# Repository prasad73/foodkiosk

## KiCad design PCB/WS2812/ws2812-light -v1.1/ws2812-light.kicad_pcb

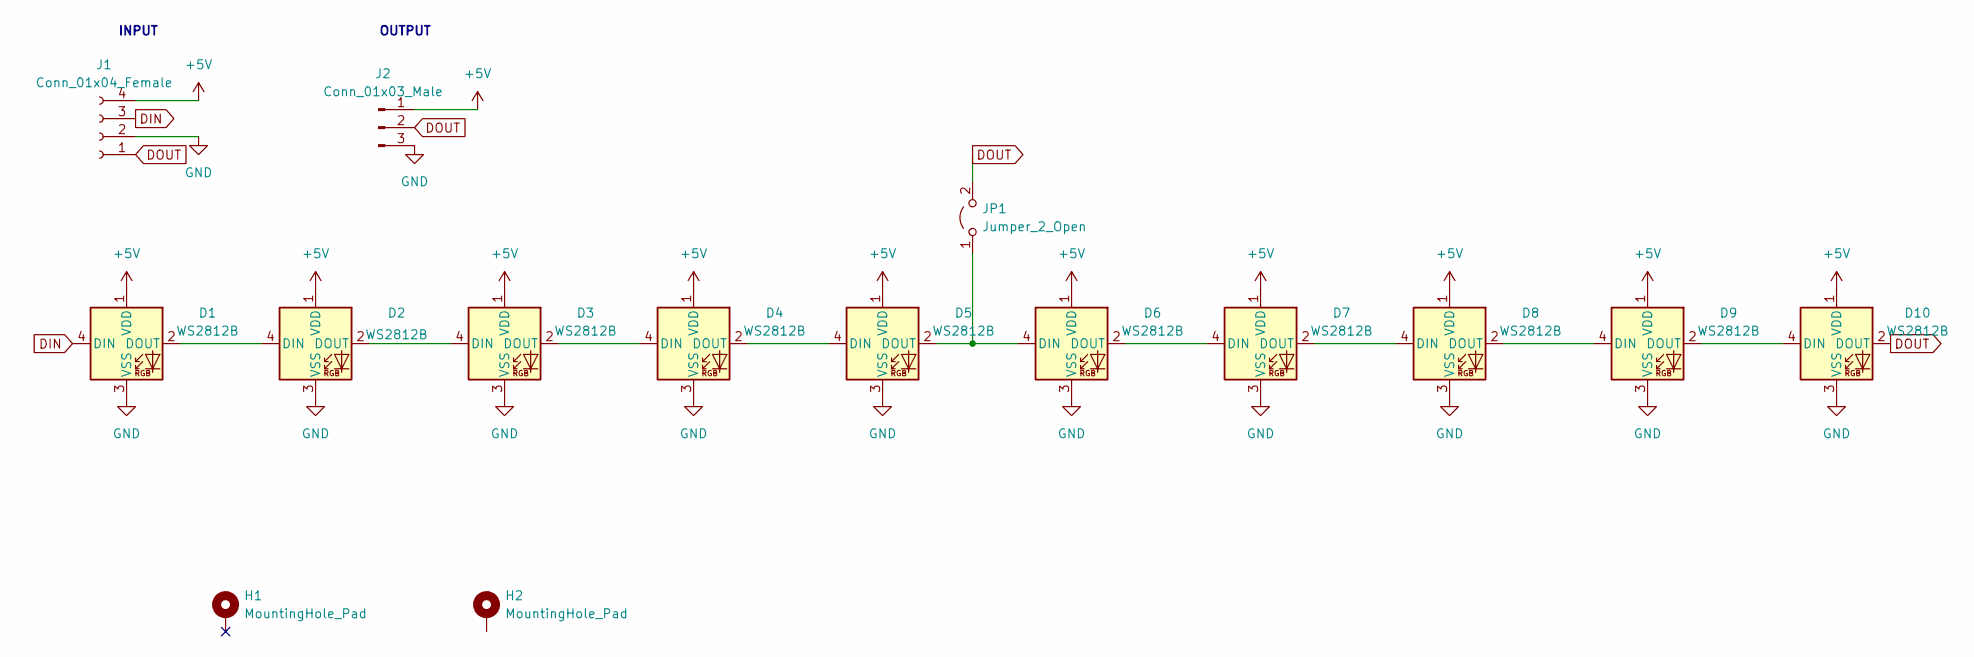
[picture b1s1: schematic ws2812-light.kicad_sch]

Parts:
D1, D2, D3, D4, D5, D6, D7, D8, D9, D10: WS2812B; LED_WS2812B_PLCC4_5.0x5.0mm_P3.2mm
H1, H2: MountingHole_Pad; MountingHole_3.2mm_M3_ISO7380_Pad
J1: Conn_01x04_Female; JST_XH_B4B-XH-A_1x04_P2.50mm_Vertical
J2: Conn_01x03_Male; PinHeader_1x03_P2.54mm_Vertical
JP1: Jumper_2_Open; SolderJumper-2_P1.3mm_Open_RoundedPad1.0x1.5mm

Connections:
+5V: D1.1 (VDD), D2.1 (VDD), D3.1 (VDD), D4.1 (VDD), D5.1 (VDD), D6.1 (VDD), D7.1 (VDD), D8.1 (VDD), D9.1 (VDD), D10.1 (VDD), J1.4, J2.1
DIN: D1.4 (DIN), J1.3
DOUT: D10.2 (DOUT), J1.1, J2.2, JP1.2 (B)
GND: D1.3 (VSS), D2.3 (VSS), D3.3 (VSS), D4.3 (VSS), D5.3 (VSS), D6.3 (VSS), D7.3 (VSS), D8.3 (VSS), D9.3 (VSS), D10.3 (VSS), J1.2, J2.3
unnamed: D1.2 (DOUT), D2.4 (DIN)
unnamed: D2.2 (DOUT), D3.4 (DIN)
unnamed: D3.2 (DOUT), D4.4 (DIN)
unnamed: D4.2 (DOUT), D5.4 (DIN)
unnamed: D5.2 (DOUT), D6.4 (DIN), JP1.1 (A)
unnamed: D6.2 (DOUT), D7.4 (DIN)
unnamed: D7.2 (DOUT), D8.4 (DIN)
unnamed: D8.2 (DOUT), D9.4 (DIN)
unnamed: D9.2 (DOUT), D10.4 (DIN)

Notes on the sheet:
INPUT
OUTPUT

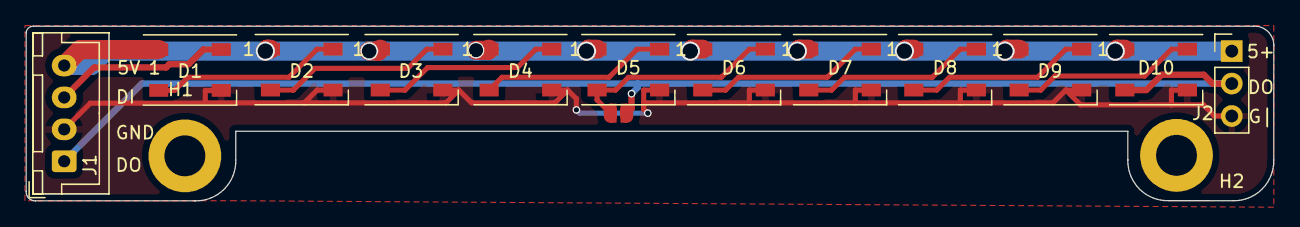
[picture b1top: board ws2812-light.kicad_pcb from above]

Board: 2 copper layers, 97.7 x 13.7 mm, 16 parts (1 on the bottom side), 13 nets.

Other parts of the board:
G2: LOGO; Verifygn-Logo-Tiny

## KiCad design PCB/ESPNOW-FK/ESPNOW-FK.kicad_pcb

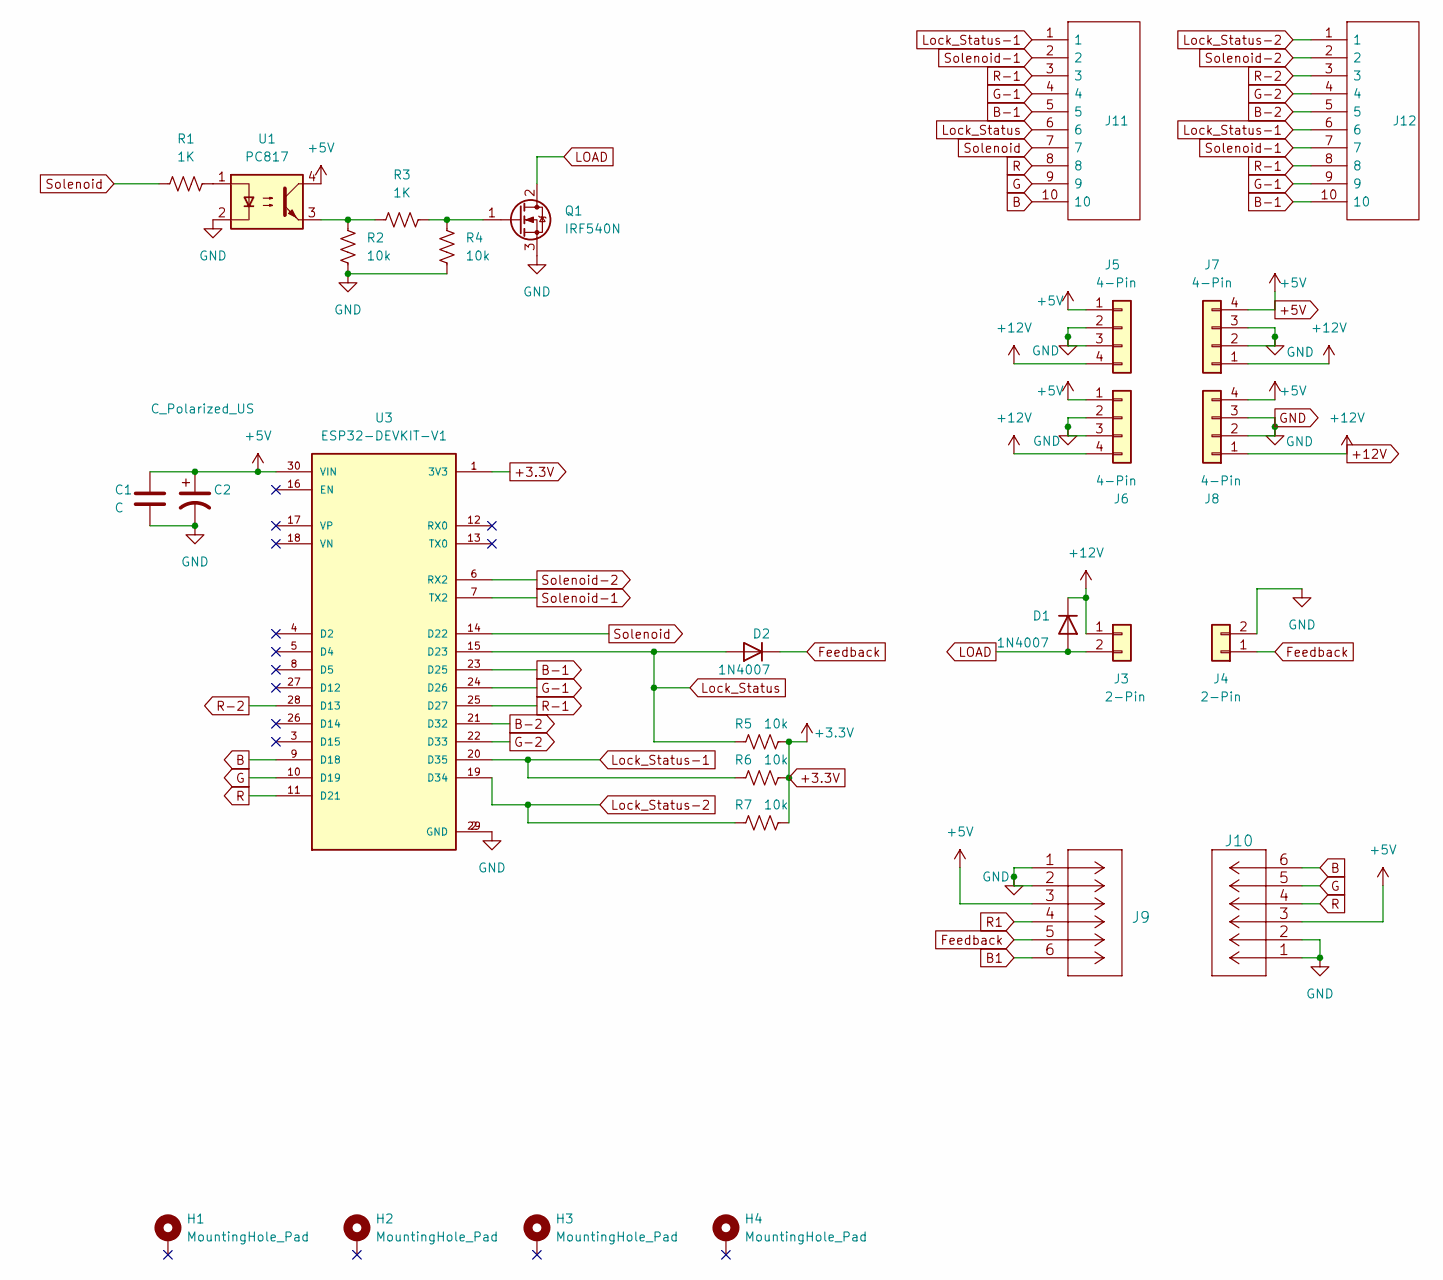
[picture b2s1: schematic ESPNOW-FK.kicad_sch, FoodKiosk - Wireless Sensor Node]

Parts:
C1: C; C_Disc_D5.0mm_W2.5mm_P5.00mm
C2: C_Polarized_US; CP_Radial_D8.0mm_P5.00mm
D1, D2: 1N4007; D_DO-41_SOD81_P10.16mm_Horizontal
H1, H2, H3, H4: MountingHole_Pad; MountingHole_3.7mm_Pad
J3, J4: 2-Pin; JST_XH_1x02_P2.50mm_Vertical
J5, J7: 4-Pin; TerminalBlock_Phoenix_1x04_P5.08mm_Horizontal
J6, J8: 4-Pin; JST_XH_1x04_P2.50mm_Vertical
J9, J10: 6-Pin; JST_XH_1x06_P2.50mm_Vertical
J11, J12: 10-Pin; JST_XH_1x10_P2.50mm_Vertical; Manufacturer_Part_Number 1792944; Mouser Part Number 651-1792944
Q1: IRF540N; TO-220-3_Vertical
R1, R3: 1K; R_Axial_DIN0207_L6.3mm_D2.5mm_P10.16mm_Horizontal
R2, R4, R5, R6, R7: 10k; R_Axial_DIN0207_L6.3mm_D2.5mm_P10.16mm_Horizontal
U1: PC817; DIP-4_W7.62mm
U3: ESP32-DEVKIT-V1; MODULE_ESP32_DEVKIT_V1; PARTREV N/A

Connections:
+3.3V: R5.2, R6.2, R7.2, U3.1 (3V3)
+5V: C1.1, C2.1, J5.1, J6.1, J7.4, J8.4, J9.3, J10.3, U1.4, U3.30 (VIN)
+12V: D1.1 (K), J3.1, J5.4, J6.4, J7.1, J8.1
B: J10.6, J11.10, U3.9 (D18)
B1: J9.6
B-1: J11.5, J12.10, U3.23 (D25)
B-2: J12.5, U3.21 (D32)
Feedback: D2.1 (K), J4.1, J9.5
G: J10.5, J11.9, U3.10 (D19)
G-1: J11.4, J12.9, U3.24 (D26)
G-2: J12.4, U3.22 (D33)
GND: C1.2, C2.2, J4.2, J5.2, J5.3, J6.2, J6.3, J7.2, J7.3, J8.2, J8.3, J9.1, J9.2, J10.1, J10.2, Q1.3 (S), R2.2, R4.2, U1.2, U3.2 (GND), U3.29 (GND)
LOAD: D1.2 (A), J3.2, Q1.2 (D)
Lock_Status: D2.2 (A), J11.6, R5.1, U3.15 (D23)
Lock_Status-1: J11.1, J12.6, R6.1, U3.20 (D35)
Lock_Status-2: J12.1, R7.1, U3.19 (D34)
unnamed: Q1.1 (G), R3.2, R4.1
unnamed: R1.2, U1.1
unnamed: R2.1, R3.1, U1.3
R: J10.4, J11.8, U3.11 (D21)
R1: J9.4
R-1: J11.3, J12.8, U3.25 (D27)
R-2: J12.3, U3.28 (D13)
Solenoid: J11.7, R1.1, U3.14 (D22)
Solenoid-1: J11.2, J12.7, U3.7 (TX2)
Solenoid-2: J12.2, U3.6 (RX2)

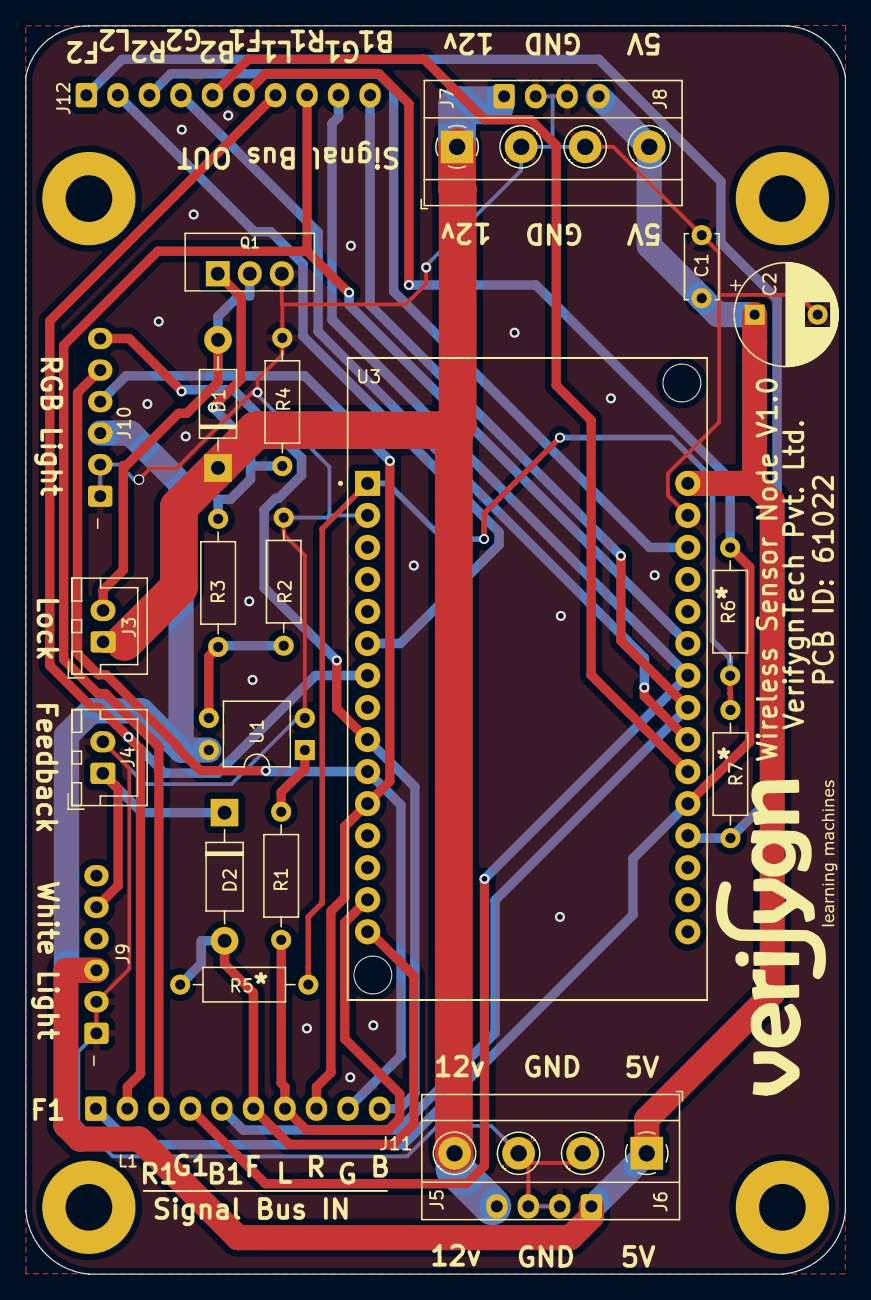
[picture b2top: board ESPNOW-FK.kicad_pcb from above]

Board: 2 copper layers, 65.0 x 99.0 mm, 30 parts (1 on the bottom side), 24 nets.

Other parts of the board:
G12132: LOGO; Verifygn-Logo-Small
G*3e2: LOGO; Verifygn-Logo-Small

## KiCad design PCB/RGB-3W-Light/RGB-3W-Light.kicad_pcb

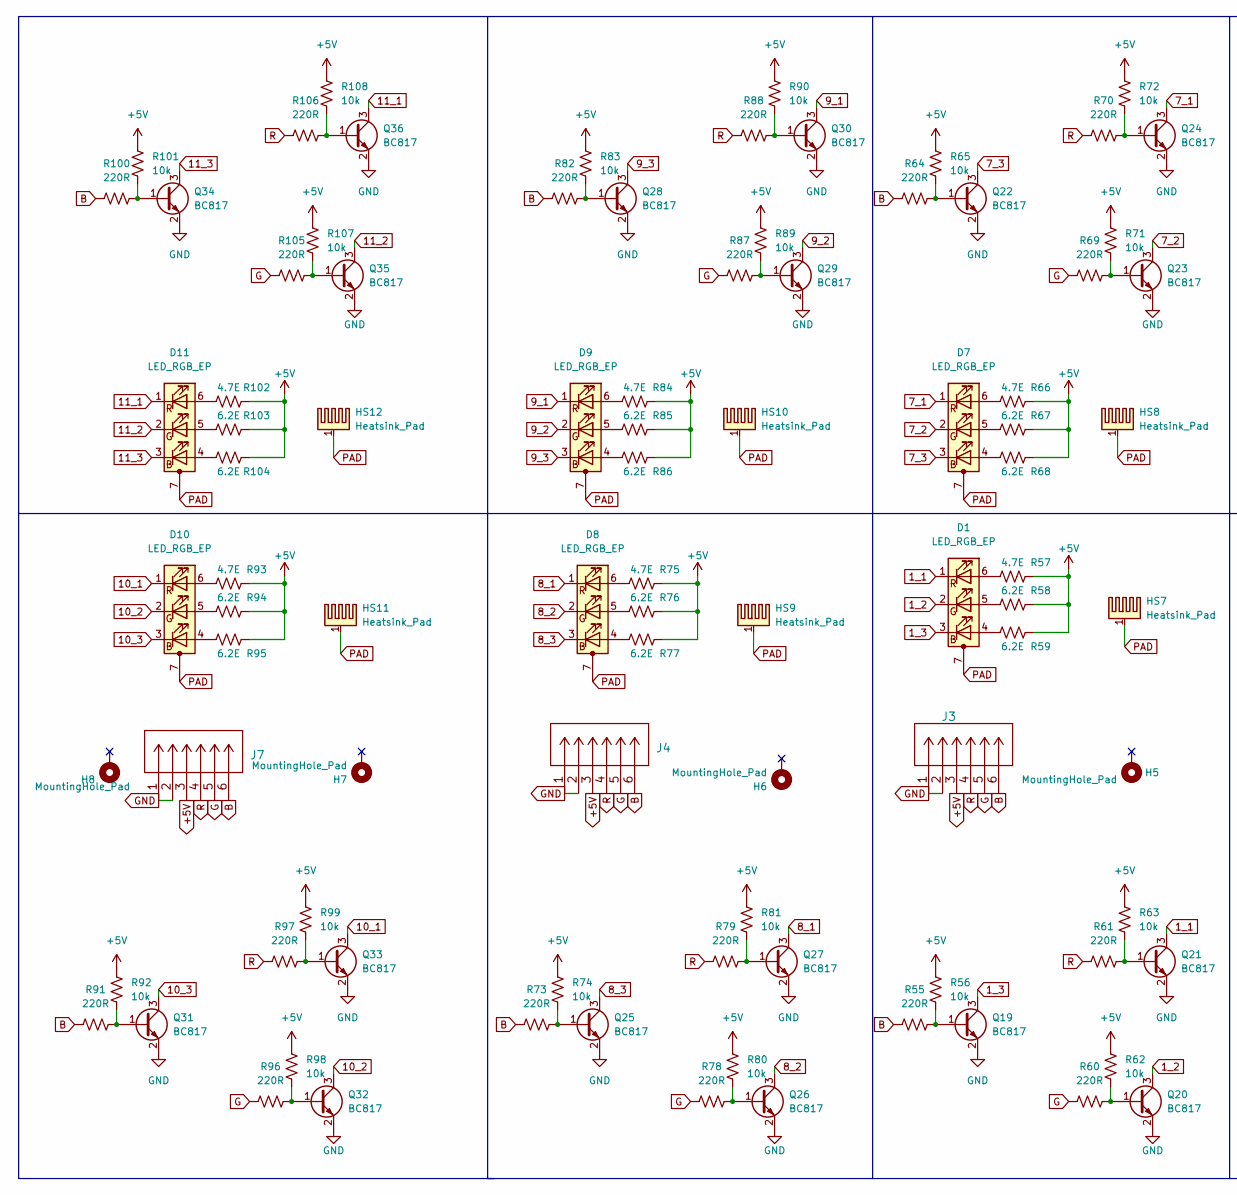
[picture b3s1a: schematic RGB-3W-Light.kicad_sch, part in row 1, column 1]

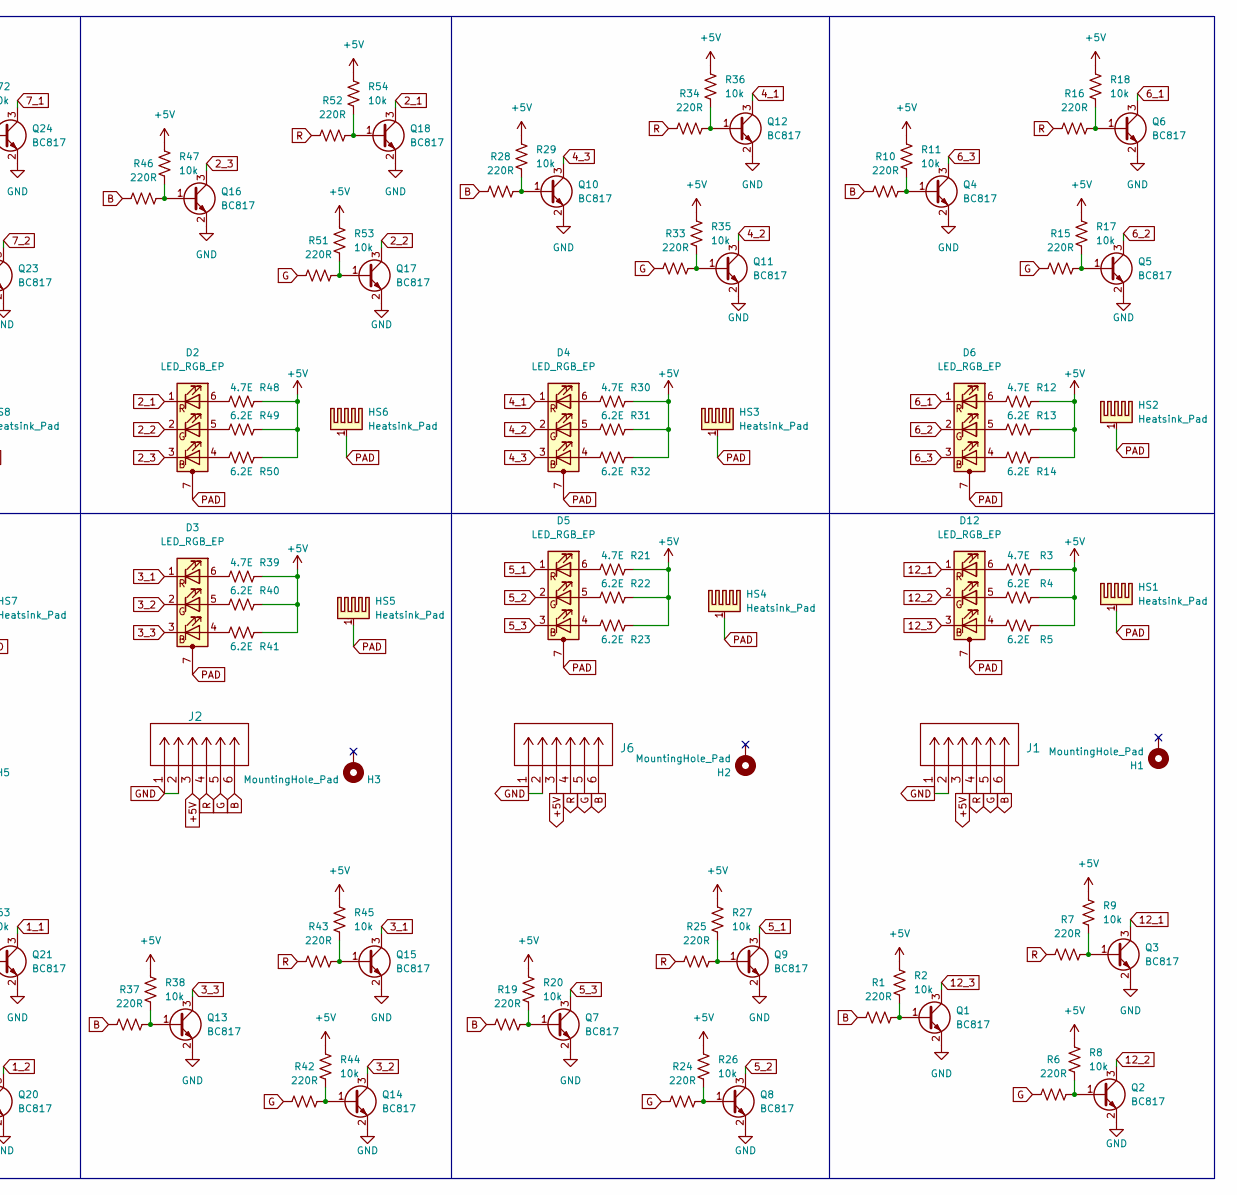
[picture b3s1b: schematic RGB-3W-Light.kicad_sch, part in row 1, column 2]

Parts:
D1, D2, D3, D4, D5, D6, D7, D8, D9, D10, D11, D12: LED_RGB_EP; LED_RGB_GT-P6PRGB4303
H1, H2, H3, H5, H6, H7, H8: MountingHole_Pad; MountingHole_3.5mm_Pad_Via
HS1, HS4, HS5, HS7, HS9, HS11: Heatsink_Pad; LED_COOLING_PAD
HS2, HS3, HS6, HS8, HS10: Heatsink_Pad; LED_COOLING_PAD-2
HS12: Heatsink_Pad; LED_COOLING_PAD-3
J1, J2, J3, J4, J6, J7: 6-Pin; JST_XH_1x06_P2.50mm_Vertical
Q1, Q2, Q3, Q4, Q5, Q6, Q7, Q8, Q9, Q10, Q11, Q12, Q13, Q14, Q15, Q16, Q17, Q18, Q19, Q20, Q21, Q22, Q23, Q24, Q25, Q26, Q27, Q28, Q29, Q30, Q31, Q32, Q33, Q34, Q35, Q36: BC817; SOT-23
R1, R6, R7, R10, R15, R16, R19, R24, R25, R28, R33, R34, R37, R42, R43, R46, R51, R52, R55, R60, R61, R64, R69, R70, R73, R78, R79, R82, R87, R88, R91, R96, R97, R100, R105, R106: 220R; R_0805_2012Metric_Pad1.20x1.40mm_HandSolder
R2, R8, R9, R11, R17, R18, R20, R26, R27, R29, R35, R36, R38, R44, R45, R47, R53, R54, R56, R62, R63, R65, R71, R72, R74, R80, R81, R83, R89, R90, R92, R98, R99, R101, R107, R108: 10k; R_0805_2012Metric_Pad1.20x1.40mm_HandSolder
R3, R12, R21, R30, R39, R48, R57, R66, R75, R84, R93, R102: 4.7E; R_2512_6332Metric_Pad1.40x3.35mm_HandSolder
R4, R5, R13, R14, R22, R23, R31, R32, R40, R41, R49, R50, R58, R59, R67, R68, R76, R77, R85, R86, R94, R95, R103, R104: 6.2E; R_2512_6332Metric_Pad1.40x3.35mm_HandSolder

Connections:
1_1: D1.1 (RK), Q21.3 (C)
1_2: D1.2 (GK), Q20.3 (C)
1_3: D1.3 (BK), Q19.3 (C)
2_1: D2.1 (RK), Q18.3 (C)
2_2: D2.2 (GK), Q17.3 (C)
2_3: D2.3 (BK), Q16.3 (C)
3_1: D3.1 (RK), Q15.3 (C)
3_2: D3.2 (GK), Q14.3 (C)
3_3: D3.3 (BK), Q13.3 (C)
4_1: D4.1 (RK), Q12.3 (C)
4_2: D4.2 (GK), Q11.3 (C)
4_3: D4.3 (BK), Q10.3 (C)
5_1: D5.1 (RK), Q9.3 (C)
5_2: D5.2 (GK), Q8.3 (C)
5_3: D5.3 (BK), Q7.3 (C)
6_1: D6.1 (RK), Q6.3 (C)
6_2: D6.2 (GK), Q5.3 (C)
6_3: D6.3 (BK), Q4.3 (C)
7_1: D7.1 (RK), Q24.3 (C)
7_2: D7.2 (GK), Q23.3 (C)
7_3: D7.3 (BK), Q22.3 (C)
8_1: D8.1 (RK), Q27.3 (C)
8_2: D8.2 (GK), Q26.3 (C)
8_3: D8.3 (BK), Q25.3 (C)
9_1: D9.1 (RK), Q30.3 (C)
9_2: D9.2 (GK), Q29.3 (C)
9_3: D9.3 (BK), Q28.3 (C)
10_1: D10.1 (RK), Q33.3 (C)
10_2: D10.2 (GK), Q32.3 (C)
10_3: D10.3 (BK), Q31.3 (C)
11_1: D11.1 (RK), Q36.3 (C)
11_2: D11.2 (GK), Q35.3 (C)
11_3: D11.3 (BK), Q34.3 (C)
12_1: D12.1 (RK), Q3.3 (C)
12_2: D12.2 (GK), Q2.3 (C)
12_3: D12.3 (BK), Q1.3 (C)
+5V: J1.3, J2.3, J3.3, J4.3, J6.3, J7.3, R2.1, R3.1, R4.1, R5.1, R8.1, R9.1, R11.1, R12.1, R13.1, R14.1, R17.1, R18.1, R20.1, R21.1, R22.1, R23.1, R26.1, R27.1, R29.1, R30.1, R31.1, R32.1, R35.1, R36.1, R38.1, R39.1, R40.1, R41.1, R44.1, R45.1, R47.1, R48.1, R49.1, R50.1, R53.1, R54.1, R56.1, R57.1, R58.1, R59.1, R62.1, R63.1, R65.1, R66.1, R67.1, R68.1, R71.1, R72.1, R74.1, R75.1, R76.1, R77.1, R80.1, R81.1, R83.1, R84.1, R85.1, R86.1, R89.1, R90.1, R92.1, R93.1, R94.1, R95.1, R98.1, R99.1, R101.1, R102.1, R103.1, R104.1, R107.1, R108.1
B: J1.6, J2.6, J3.6, J4.6, J6.6, J7.6, R1.1, R10.1, R19.1, R28.1, R37.1, R46.1, R55.1, R64.1, R73.1, R82.1, R91.1, R100.1
G: J1.5, J2.5, J3.5, J4.5, J6.5, J7.5, R6.1, R15.1, R24.1, R33.1, R42.1, R51.1, R60.1, R69.1, R78.1, R87.1, R96.1, R105.1
GND: J1.1, J1.2, J2.1, J2.2, J3.1, J3.2, J4.1, J4.2, J6.1, J6.2, J7.1, J7.2, Q1.2 (E), Q2.2 (E), Q3.2 (E), Q4.2 (E), Q5.2 (E), Q6.2 (E), Q7.2 (E), Q8.2 (E), Q9.2 (E), Q10.2 (E), Q11.2 (E), Q12.2 (E), Q13.2 (E), Q14.2 (E), Q15.2 (E), Q16.2 (E), Q17.2 (E), Q18.2 (E), Q19.2 (E), Q20.2 (E), Q21.2 (E), Q22.2 (E), Q23.2 (E), Q24.2 (E), Q25.2 (E), Q26.2 (E), Q27.2 (E), Q28.2 (E), Q29.2 (E), Q30.2 (E), Q31.2 (E), Q32.2 (E), Q33.2 (E), Q34.2 (E), Q35.2 (E), Q36.2 (E)
unnamed: D1.4 (BA), R59.2
unnamed: D1.5 (GA), R58.2
unnamed: D1.6 (RA), R57.2
unnamed: D2.4 (BA), R50.2
unnamed: D2.5 (GA), R49.2
unnamed: D2.6 (RA), R48.2
unnamed: D3.4 (BA), R41.2
unnamed: D3.5 (GA), R40.2
unnamed: D3.6 (RA), R39.2
unnamed: D4.4 (BA), R32.2
unnamed: D4.5 (GA), R31.2
unnamed: D4.6 (RA), R30.2
unnamed: D5.4 (BA), R23.2
unnamed: D5.5 (GA), R22.2
unnamed: D5.6 (RA), R21.2
unnamed: D6.4 (BA), R14.2
unnamed: D6.5 (GA), R13.2
unnamed: D6.6 (RA), R12.2
unnamed: D7.4 (BA), R68.2
unnamed: D7.5 (GA), R67.2
unnamed: D7.6 (RA), R66.2
unnamed: D8.4 (BA), R77.2
unnamed: D8.5 (GA), R76.2
unnamed: D8.6 (RA), R75.2
unnamed: D9.4 (BA), R86.2
unnamed: D9.5 (GA), R85.2
unnamed: D9.6 (RA), R84.2
unnamed: D10.4 (BA), R95.2
unnamed: D10.5 (GA), R94.2
unnamed: D10.6 (RA), R93.2
unnamed: D11.4 (BA), R104.2
unnamed: D11.5 (GA), R103.2
unnamed: D11.6 (RA), R102.2
unnamed: D12.4 (BA), R5.2
unnamed: D12.5 (GA), R4.2
unnamed: D12.6 (RA), R3.2
unnamed: Q1.1 (B), R1.2, R2.2
unnamed: Q2.1 (B), R6.2, R8.2
unnamed: Q3.1 (B), R7.2, R9.2
unnamed: Q4.1 (B), R10.2, R11.2
unnamed: Q5.1 (B), R15.2, R17.2
unnamed: Q6.1 (B), R16.2, R18.2
unnamed: Q7.1 (B), R19.2, R20.2
unnamed: Q8.1 (B), R24.2, R26.2
unnamed: Q9.1 (B), R25.2, R27.2
unnamed: Q10.1 (B), R28.2, R29.2
unnamed: Q11.1 (B), R33.2, R35.2
unnamed: Q12.1 (B), R34.2, R36.2
unnamed: Q13.1 (B), R37.2, R38.2
unnamed: Q14.1 (B), R42.2, R44.2
unnamed: Q15.1 (B), R43.2, R45.2
unnamed: Q16.1 (B), R46.2, R47.2
unnamed: Q17.1 (B), R51.2, R53.2
unnamed: Q18.1 (B), R52.2, R54.2
unnamed: Q19.1 (B), R55.2, R56.2
unnamed: Q20.1 (B), R60.2, R62.2
unnamed: Q21.1 (B), R61.2, R63.2
unnamed: Q22.1 (B), R64.2, R65.2
unnamed: Q23.1 (B), R69.2, R71.2
unnamed: Q24.1 (B), R70.2, R72.2
unnamed: Q25.1 (B), R73.2, R74.2
unnamed: Q26.1 (B), R78.2, R80.2
unnamed: Q27.1 (B), R79.2, R81.2
unnamed: Q28.1 (B), R82.2, R83.2
unnamed: Q29.1 (B), R87.2, R89.2
unnamed: Q30.1 (B), R88.2, R90.2
unnamed: Q31.1 (B), R91.2, R92.2
unnamed: Q32.1 (B), R96.2, R98.2
unnamed: Q33.1 (B), R97.2, R99.2
unnamed: Q34.1 (B), R100.2, R101.2
unnamed: Q35.1 (B), R105.2, R107.2
unnamed: Q36.1 (B), R106.2, R108.2
PAD: D1.7 (PAD), D2.7 (PAD), D3.7 (PAD), D4.7 (PAD), D5.7 (PAD), D6.7 (PAD), D7.7 (PAD), D8.7 (PAD), D9.7 (PAD), D10.7 (PAD), D11.7 (PAD), D12.7 (PAD), HS1.1, HS2.1, HS3.1, HS4.1, HS5.1, HS6.1, HS7.1, HS8.1, HS9.1, HS10.1, HS11.1, HS12.1
R: J1.4, J2.4, J3.4, J4.4, J6.4, J7.4, R7.1, R16.1, R25.1, R34.1, R43.1, R52.1, R61.1, R70.1, R79.1, R88.1, R97.1, R106.1

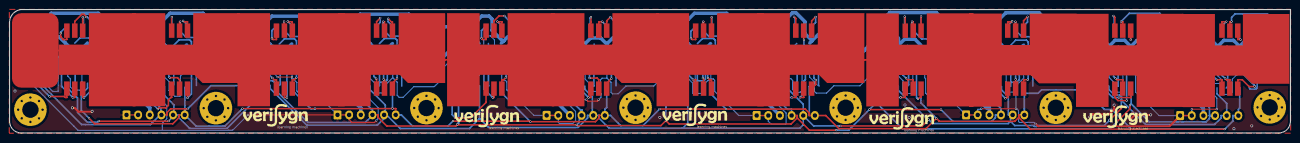
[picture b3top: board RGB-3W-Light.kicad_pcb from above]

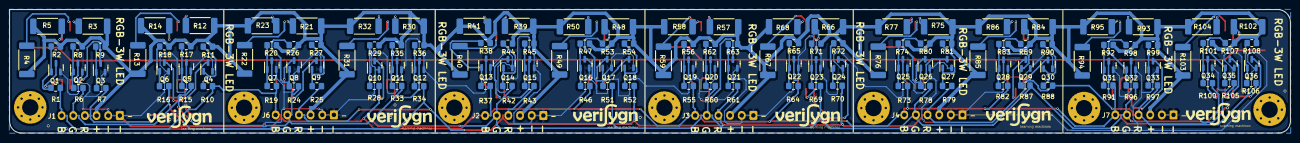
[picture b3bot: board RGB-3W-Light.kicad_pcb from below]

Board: 2 copper layers, 275.0 x 26.5 mm, 192 parts (156 on the bottom side), 114 nets.

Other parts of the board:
G21321, G21321#2, G21321#3, G21321#4, G21321#5, G21321#6, G21321#7, G21321#8, G21321#9, G21321#10, G21321#11: LOGO; Verifygn-Logo-Tiny

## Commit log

2022-09-20 Version1.0-Under Development
2022-09-28 Under Testing Phase
2022-11-03 Version1-Under Progress
2022-11-15 Updated Source code- Ready for testing
2022-11-23 Arduino Firmware Updated version - deployed in realtime environment
2022-11-23 RPi kiosk firmware - updated
2023-01-20 Version2.0 PCB Files (Kiosk-2)
2023-02-27 Kiosk-2 files under process
2023-03-03 Working code - Exhibition(Kiosk2)
2023-03-03 Updated Exhibition.ino file -working tested
2023-03-03 Tested Python Script for display
2023-03-03 Working file with Kiosk-2
2023-03-30 Under development file kiosk-1 version 1.1
2023-04-01 Kiosk-1.1 updated test code - working
2023-04-05 Updated ESP32 underdevelopment file for Kiosk1.1
2023-04-17 updated kiosk-1 code working
2023-04-20 Kiosk -Mot Firmware-1.1
    Hardware -MEGA + ESP32(WIFI)
    Deployment Code
2023-04-22 Upgraded Files -Kiosk1 and Kiosk2 - Unverified
2023-04-23 Kiosk-2 Working Code - Verified
2023-05-22 Kiosk-3 Test files - Under Development
2023-08-04 1. Re-organized Files associated for every Individual Kiosk, added readme files 2. Verified links and API
2023-08-04 Test Code(under Development) Web Interface offline
2023-08-24 Updated files till kiosk-5 (Kiosk-5 Under development)
2023-08-24 Upgraded version kiosk 5 under development
2023-09-25 Under development
2023-10-17 Kiosk5 Firmware v1.3 Tested ok Code
2023-11-04 Kiosk1 and Kiosk2 Latest deployed firmware - tested and Working Code
2023-12-22 Kios5 - New Feature(Manual Control mode) under Development
2023-12-28 Kiosk5 - online+offline mode added
